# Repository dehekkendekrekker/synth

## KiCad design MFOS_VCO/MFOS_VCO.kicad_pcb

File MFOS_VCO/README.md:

# MFOS_VCO

A KiCAD conversion from MFOS's VCO design as posted [here](http://musicfromouterspace.com/index.php?MAINTAB=SYNTHDIY&PROJARG=WAVEFORMER2015/WAVEFORMER2015.php&VPW=1273&VPH=1194)

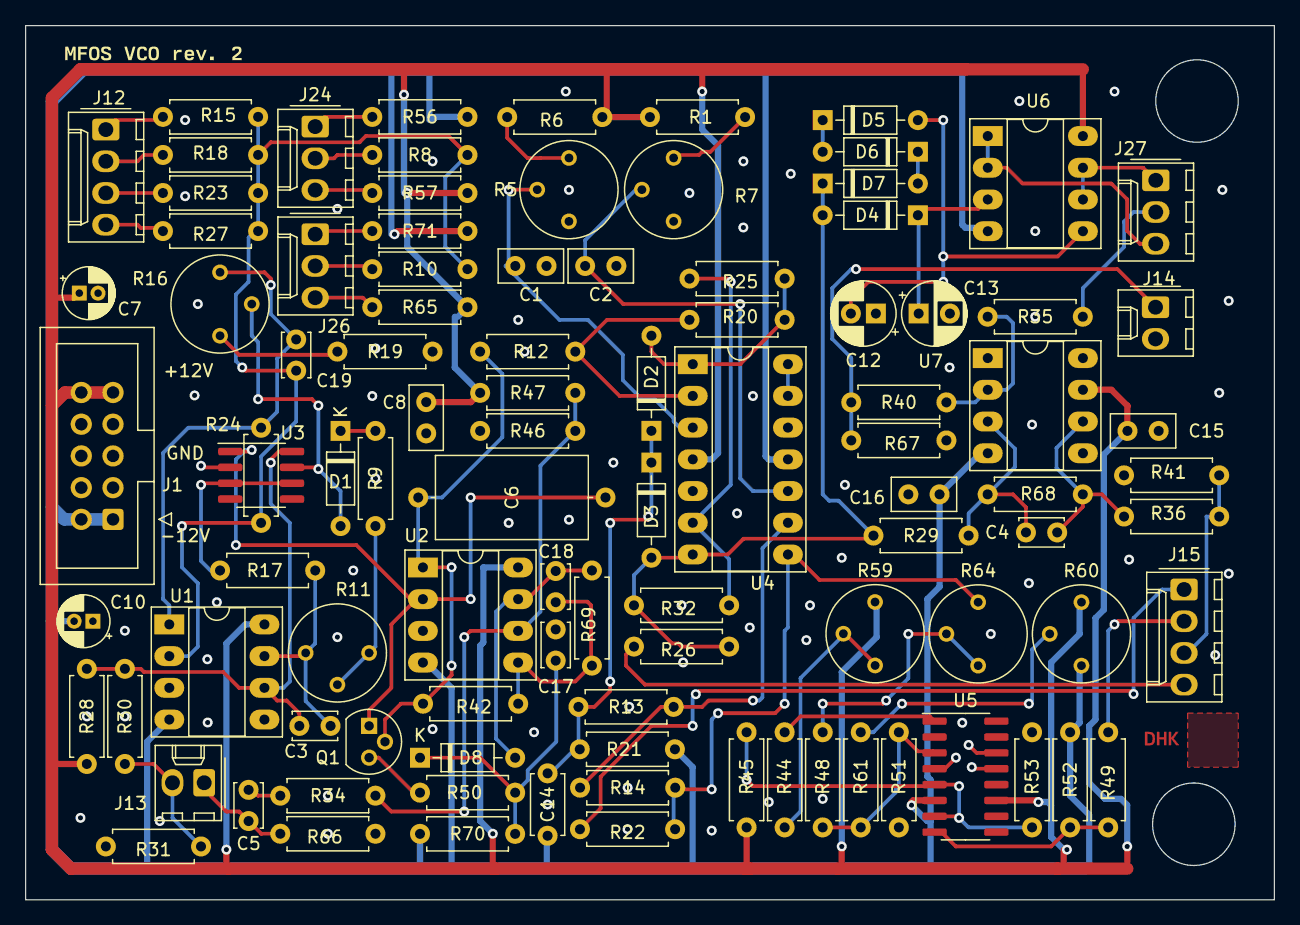
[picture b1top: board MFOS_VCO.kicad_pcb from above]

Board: 4 copper layers, 100.0 x 70.0 mm, 101 parts (0 on the bottom side), 66 nets.

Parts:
C1, C2, C8, C15, C16: 0.1uF; C_Disc_D5.0mm_W2.5mm_P2.50mm
C3, C17, C19: 100pF; C_Disc_D3.4mm_W2.1mm_P2.50mm
C4: 10pF; C_Disc_D3.4mm_W2.1mm_P2.50mm
C5: 0.001uF; C_Disc_D3.4mm_W2.1mm_P2.50mm
C6: .005uF; C_Axial_L12.0mm_D6.5mm_P15.00mm_Horizontal
C7, C10: 10uF; CP_Radial_D4.0mm_P1.50mm
C12: 1uF; CP_Radial_D5.0mm_P2.00mm
C13: 1uF; CP_Radial_D5.0mm_P2.50mm
C14: 0.002uF; C_Disc_D4.7mm_W2.5mm_P5.00mm
C18: 4.7pF; C_Disc_D3.4mm_W2.1mm_P2.50mm
D1, D2, D3, D4, D5, D6, D7, D8: 1N914; D_DO-35_SOD27_P7.62mm_Horizontal
J1: Conn_02x05_Odd_Even; IDC-Header_2x05_P2.54mm_Vertical
J12, J15: Conn_01x04; Molex_KK-254_AE-6410-04A_1x04_P2.54mm_Vertical
J13, J14: Conn_01x02; Molex_KK-254_AE-6410-02A_1x02_P2.54mm_Vertical
J24, J26, J27: Conn_01x03; Molex_KK-254_AE-6410-03A_1x03_P2.54mm_Vertical
Q1: PN4391; TO-92
R1, R12, R13, R17, R25, R32, R35, R40, R42, R47, R71: 10k; R_Axial_DIN0207_L6.3mm_D2.5mm_P7.62mm_Horizontal
R5, R7: 10k; Potentiometer_Bourns_3339P_Vertical
R6, R10, R15, R18, R23, R27, R29, R31, R44, R50, R66, R67: 100k; R_Axial_DIN0207_L6.3mm_D2.5mm_P7.62mm_Horizontal
R8, R28, R30, R45, R69: 1M; R_Axial_DIN0207_L6.3mm_D2.5mm_P7.62mm_Horizontal
R9, R36, R52: 4.7k; R_Axial_DIN0207_L6.3mm_D2.5mm_P7.62mm_Horizontal
R11, R60, R64: 100k; Potentiometer_Bourns_3339P_Vertical
R14, R21, R48: 20k; R_Axial_DIN0207_L6.3mm_D2.5mm_P7.62mm_Horizontal
R16: 100; Potentiometer_Bourns_3339P_Vertical
R19: 475; R_Axial_DIN0207_L6.3mm_D2.5mm_P7.62mm_Horizontal
R20, R65: 47k; R_Axial_DIN0207_L6.3mm_D2.5mm_P7.62mm_Horizontal
R22, R26, R34, R49, R51: 1k; R_Axial_DIN0207_L6.3mm_D2.5mm_P7.62mm_Horizontal
R24: 1.5k; R_Axial_DIN0207_L6.3mm_D2.5mm_P7.62mm_Horizontal
R41: 3k; R_Axial_DIN0207_L6.3mm_D2.5mm_P7.62mm_Horizontal
R46: 2k; R_Axial_DIN0207_L6.3mm_D2.5mm_P7.62mm_Horizontal
R53: 130k; R_Axial_DIN0207_L6.3mm_D2.5mm_P7.62mm_Horizontal
R56, R57: 200k; R_Axial_DIN0207_L6.3mm_D2.5mm_P7.62mm_Horizontal
R59: 1M; Potentiometer_Bourns_3339P_Vertical
R61: 470k; R_Axial_DIN0207_L6.3mm_D2.5mm_P7.62mm_Horizontal
R68: 10M; R_Axial_DIN0207_L6.3mm_D2.5mm_P7.62mm_Horizontal
R70: 18k; R_Axial_DIN0207_L6.3mm_D2.5mm_P7.62mm_Horizontal
U1: OP275; DIP-8_W7.62mm_Socket_LongPads
U2, U6: TL072; DIP-8_W7.62mm_Socket_LongPads
U3: SSM2212; SOIC-8_3.9x4.9mm_P1.27mm
U4: TL074; DIP-14_W7.62mm_Socket_LongPads
U5: LM13700; SOIC-16_3.9x9.9mm_P1.27mm
U7: TL071; DIP-8_W7.62mm_Socket_LongPads
kibuzzard-65B09543: G***; kibuzzard-65B09543
kibuzzard-660EFCED: G***; kibuzzard-660EFCED

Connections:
+12V: C7.1, C8.1, C15.1, J1.9, J1.10, R1.2, R6.2, R28.2, R45.1, R47.2, R57.2, R59.3, R60.3, R65.2, U1.8 (V+), U2.8 (V+), U4.4 (V+), U5.11 (V+), U6.8 (V+), U7.7 (V+)
-12V: C10.2, C14.2, C16.1, J1.1, J1.2, R21.2, R52.2, R56.1, R60.1, R70.1, R71.1, U1.4 (V-), U2.4 (V-), U4.11 (V-), U5.6 (V-), U6.4 (V-), U7.4 (V-)
/R2P1: J26.1, R71.2
/R2P2: J26.2, R10.1
/R2P3: J26.3, R65.1
/R3P1: J24.1, R56.2
/R3P2: J24.2, R8.1
/R3P3: J24.3, R57.1
/Sheet 2/R39P1: J27.1, U6.6 (-), U6.7
/Sheet 2/R39P2: J27.2, R35.2
/Sheet 2/R39P3: J27.3, U6.1, U6.2 (-)
CV1: J12.1, R15.1
CV2: J12.2, R18.2
CV3: J12.3, R23.1
CV4: J12.4, R27.1
GND: C1.2, C2.2, C7.2, C8.2, C10.1, C12.1, C13.2, C15.2, C16.2, C17.2, J1.3, J1.4, J1.5, J1.6, J1.7, J1.8, J14.2, R5.1, R7.1, R19.2, R31.2, R41.2, R46.2, R51.2, R53.2, R66.2, R67.1, U1.3 (+), U1.5 (+), U2.3 (+), U3.2 (B1), U4.5 (+), U4.12 (+), U5.4 (-), U5.13 (-), U5.14 (+)
LIN: J13.2, R30.1, R31.1
unnamed: C1.1, R5.2, U4.3 (+)
unnamed: C2.1, R7.2, U4.10 (+)
unnamed: C3.1, R28.1, R30.2, U1.6 (-), U3.8 (C2)
unnamed: C3.2, R11.3, R17.2, U1.7
unnamed: C4.1, R29.2, R68.1, U7.3 (+)
unnamed: C4.2, R36.1, R68.2, U7.6
unnamed: C5.2, R34.1
unnamed: C6.1, Q1.1 (D), U2.2 (-), U3.1 (C1)
unnamed: C12.2, D5.2 (A), U6.5 (+)
unnamed: C13.1, D4.1 (K), U6.3 (+)
unnamed: C14.1, D2.1 (K), D3.1 (K), R13.1, R21.1
unnamed: C17.1, D8.1 (K), R50.2, R70.2
unnamed: C18.1, R42.2, R69.1, U2.5 (+)
unnamed: C18.2, D8.2 (A), R69.2, U2.7
unnamed: C19.1, R8.2, R10.2, R15.2, R18.1, R23.2, R24.1, R27.2, U1.2 (-)
unnamed: C19.2, R16.1, R24.2, U1.1
unnamed: D1.1 (K), R9.1
unnamed: D1.2 (A), R16.2, U3.7 (B2)
unnamed: D2.2 (A), R20.2, R25.2, U4.1
unnamed: D3.2 (A), D4.2 (A), D7.1 (K), R26.1, R29.1, R32.2, U4.7
unnamed: D5.1 (K), D6.2 (A)
unnamed: D6.1 (K), D7.2 (A)
unnamed: Q1.3 (G), R50.1
unnamed: R1.1, R7.3
unnamed: R5.3, R6.1
unnamed: R9.2, R11.1, R11.2
unnamed: R12.2, R20.1, U4.2 (-)
unnamed: R13.2, R14.1, U4.9 (-)
unnamed: R14.2, R22.1, R64.3, U4.8
unnamed: R16.3, R19.1
unnamed: R17.1, U3.3 (E1), U3.6 (E2)
unnamed: R25.1, R32.1, U4.6 (-)
unnamed: R34.2, R46.1, R47.1, U2.6 (-)
unnamed: R35.1, R40.2, U7.2 (-)
unnamed: R44.1, R59.1, R59.2
unnamed: R44.2, U5.1
unnamed: R45.2, R53.1, U5.5, U5.7
unnamed: R48.1, R64.1, R64.2
unnamed: R48.2, R51.1, R61.2, U5.3 (+)
unnamed: R49.1, R52.1, U5.8
unnamed: R60.2, R61.1
unnamed: U4.13 (-), U4.14
PWM: J14.1, R40.1, R67.2
RAW: C6.2, Q1.2 (S), R12.1, R42.1, U2.1
RMP: J15.4, R26.2
SIN: J15.2, R49.2
SQR: J15.3, R36.2, R41.1
SYNC: C5.1, J13.1, R66.1
TRI: J15.1, R22.2

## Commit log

2023-05-11 Grouped designs into one repo
2023-05-11 Renamed sequencer
2023-05-11 Apparently a small change
2023-05-11 Added analog part of sequencer
2023-05-13 Added audio mixer
2023-05-14 Added Quad DC Mixer
2023-05-14 Excluded some parts from board
2023-05-14 Added ring modulator
2023-05-14 Excluded pots and barrel jacks
2023-05-15 Unwrapped some nesting in projects
2023-05-15 Completed Spring reverb
2023-05-15 Completed auto panner
2023-05-15 Finished stereo mixer
2023-07-02 Updated BOM, renamed VCO > MFOS_VCO
2023-07-02 Working on BOM update script
2023-07-02 rdy for test
2023-07-02 Takanos
2023-07-02 Revision until and with audio mixer complete
2023-07-02 Reviewed BOM
2023-07-20 Designs adapted for BOM
2023-07-26 Final changes to BOM
2023-07-26 Added LICENSE
2023-11-11 Added VCF
2024-01-06 yeah yeah
2024-01-06 Split up design into different sheets
2024-01-21 Final changes
2024-01-22 Lots of headway
2024-01-23 Laying out
2024-01-23 Laid out last part of sheet 1
2024-01-24 All done
2024-04-04 Fixed PN4391 bug. Made some layout changes. Fitted molex connectors instead of pin connectors
2024-04-04 Removed rev1 gerbers
2024-04-04 Added drill files
2024-04-04 Added gerbers
2024-04-05 Some bugfixes
2024-04-06 Removed R24 from BOM (bought separately) " ;
2024-04-21 Added volume control
2024-09-26 Added frontpanel
